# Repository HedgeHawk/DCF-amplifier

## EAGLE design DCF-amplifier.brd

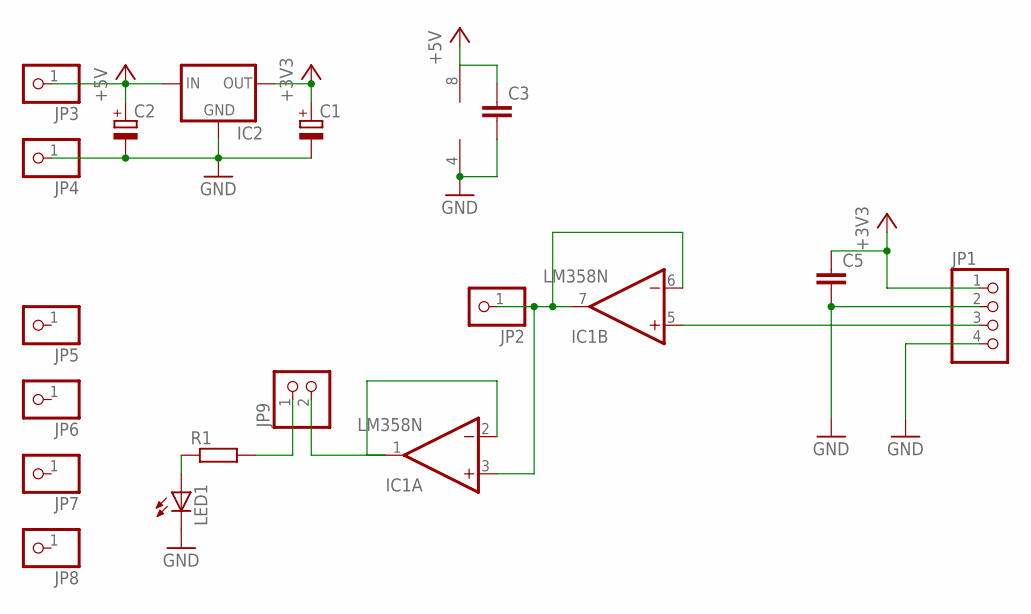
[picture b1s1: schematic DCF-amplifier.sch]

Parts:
C1, C2: CPOL-EUE2.5-5; E2,5-5
C3, C5: C-EU025-025X050; C025-025X050
IC1: LM358N; DIL08
IC2: 78XXL
JP1: PINHD-1X4; 1X04
JP2, JP3, JP4, JP5, JP6, JP7, JP8: PINHD-1X1; 1X01
JP9: PINHD-1X2; 1X02
LED1: LED5MM
R1: R-EU_0309/10; 0309/10

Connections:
+3V3: C1.+, C5.1, IC2.OUT, JP1.1
+5V: C2.+, C3.1, IC1.8 (V+), IC2.IN, JP3.1
GND: C1.-, C2.-, C3.2, C5.2, IC1.4 (V-), IC2.GND, JP1.2, JP1.4, JP4.1, LED1.K (C)
unnamed: JP9.1, R1.2
unnamed: IC1.5 (+IN), JP1.3
unnamed: LED1.A, R1.1
unnamed: IC1.3 (+IN), IC1.6 (-IN), IC1.7 (OUT), JP2.1
unnamed: IC1.1 (OUT), IC1.2 (-IN), JP9.2

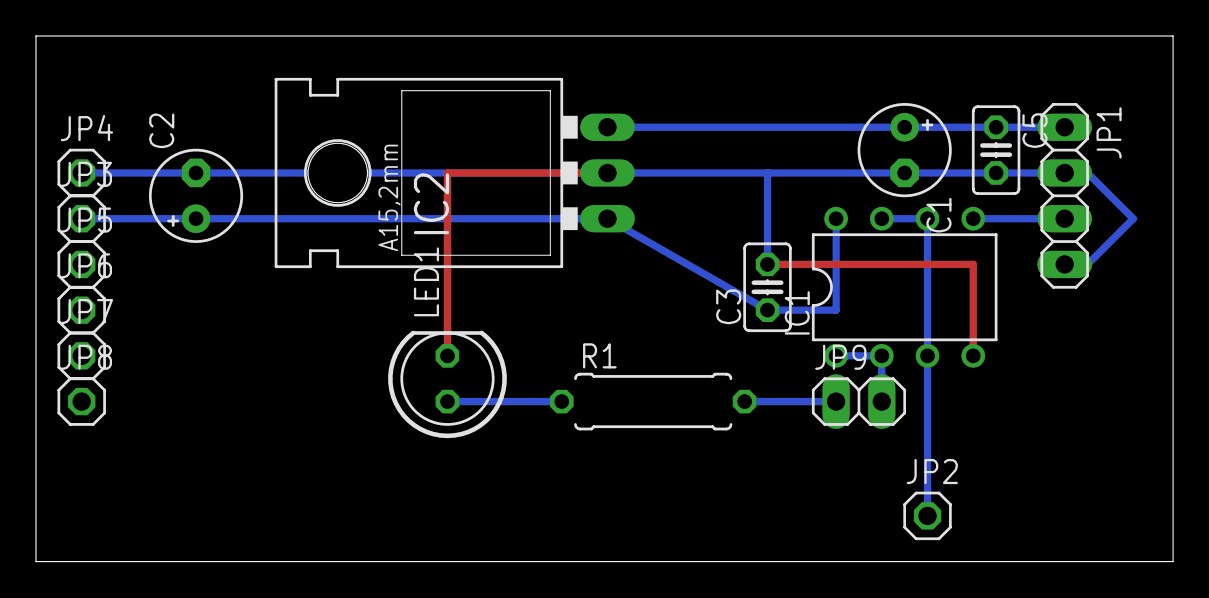
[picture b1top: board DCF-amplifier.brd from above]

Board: 2 copper layers, 63.2 x 29.2 mm, 17 parts (0 on the bottom side), 8 nets.

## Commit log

2015-09-20 :neckbeard: Added .gitattributes & .gitignore files
2015-09-20 Board and Schematic
    First prototype board layout not for manufacuring
